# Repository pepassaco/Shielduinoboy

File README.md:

# Shielduinoboy
Just a PCB Shield for the Arduino UNO of an Arduinoboy

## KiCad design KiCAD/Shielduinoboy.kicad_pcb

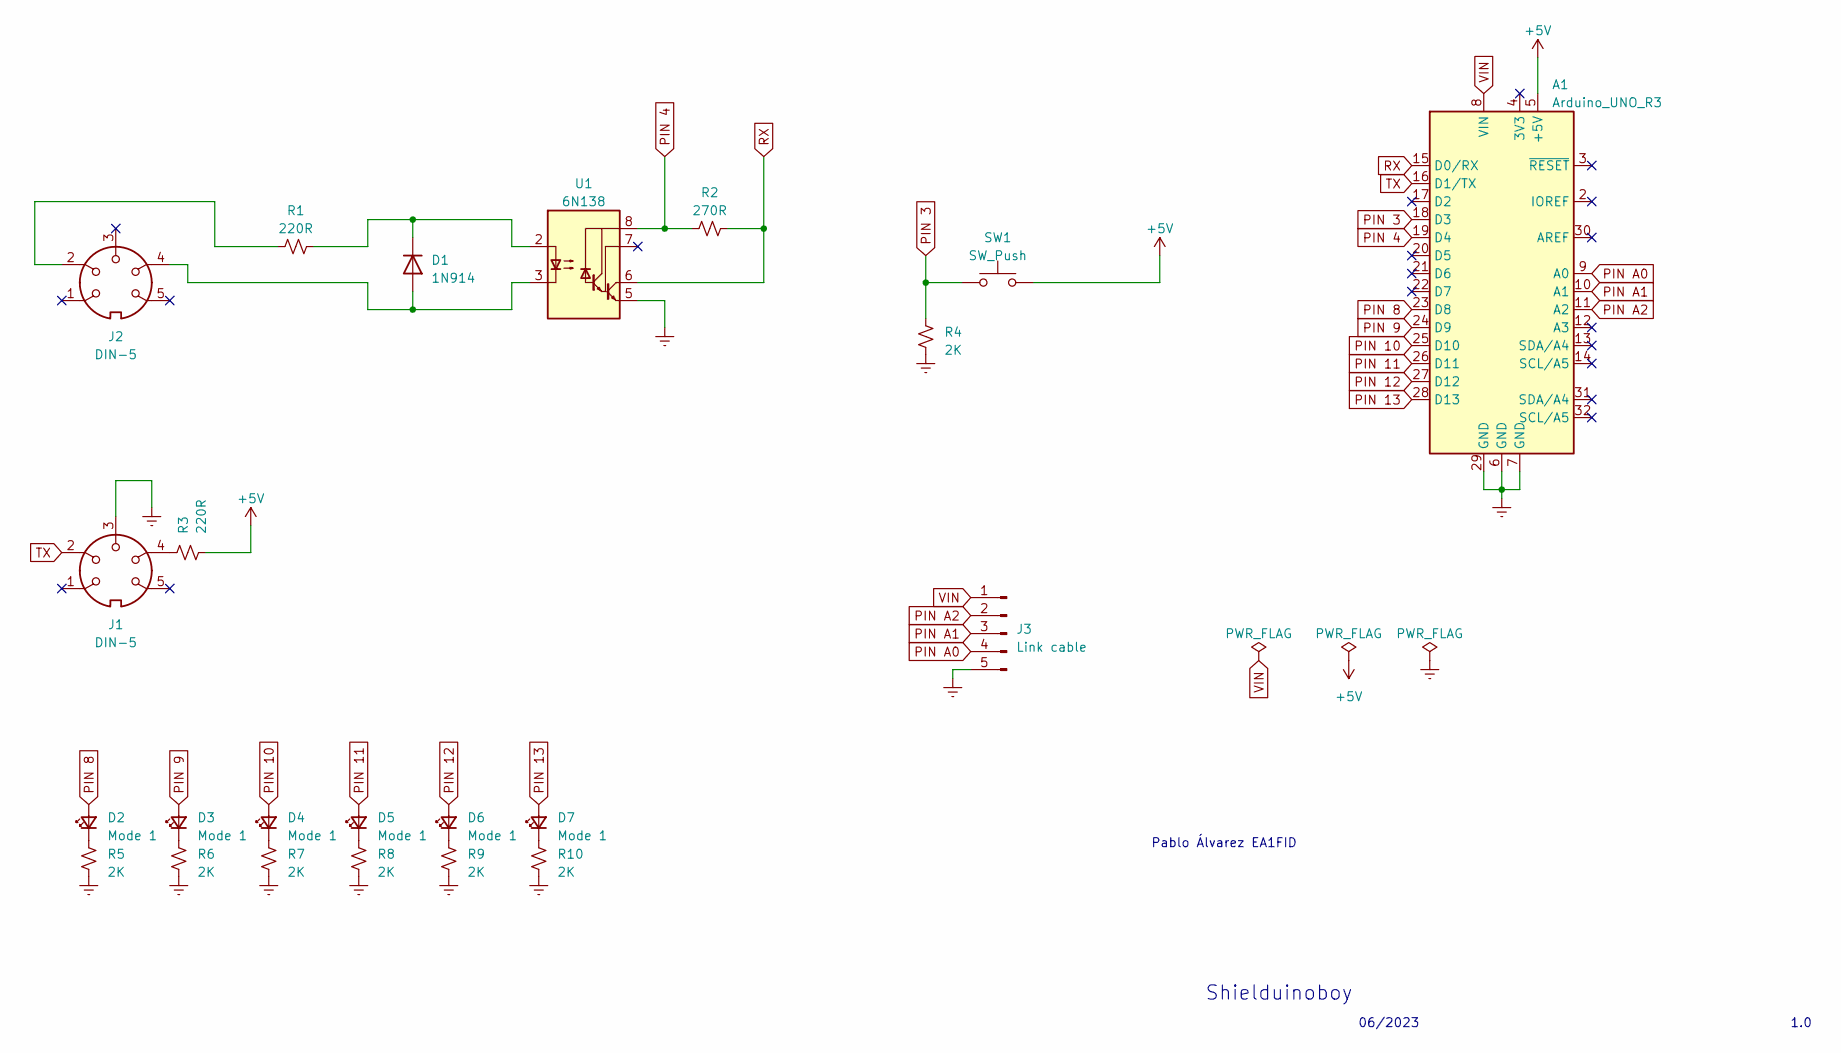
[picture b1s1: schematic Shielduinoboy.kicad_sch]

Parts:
A1: Arduino_UNO_R3; Arduino_UNO_R3_WithMountingHoles
D1: 1N914; D_DO-35_SOD27_P7.62mm_Horizontal
D2, D3, D4, D5, D6, D7: Mode 1; LED_D3.0mm
J1, J2: DIN-5; MIDI_DIN5
J3: Link cable; PinHeader_1x05_P2.54mm_Vertical
R1, R3: 220R; R_Axial_DIN0207_L6.3mm_D2.5mm_P7.62mm_Horizontal
R2: 270R; R_Axial_DIN0207_L6.3mm_D2.5mm_P7.62mm_Horizontal
R4, R5, R6, R7, R8, R9, R10: 2K; R_Axial_DIN0207_L6.3mm_D2.5mm_P7.62mm_Horizontal
SW1: SW_Push; SW_PUSH_6mm
U1: 6N138; DIP-8_W7.62mm

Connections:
+5V: A1.5 (+5V), R3.2, SW1.2
Earth: A1.6 (GND), A1.7 (GND), A1.29 (GND), J1.3, J3.5, R4.2, R5.2, R6.2, R7.2, R8.2, R9.2, R10.2, U1.5 (GND)
unnamed: D1.2 (A), J2.4, U1.3 (C2)
unnamed: D1.1 (K), R1.2, U1.2 (C1)
unnamed: D2.1 (K), R5.1
unnamed: D3.1 (K), R6.1
unnamed: D4.1 (K), R7.1
unnamed: D5.1 (K), R8.1
unnamed: D6.1 (K), R9.1
unnamed: D7.1 (K), R10.1
unnamed: J1.4, R3.1
unnamed: J2.2, R1.1
PIN 3: A1.18 (D3), R4.1, SW1.1
PIN 4: A1.19 (D4), R2.1, U1.8 (VCC)
PIN 8: A1.23 (D8), D2.2 (A)
PIN 9: A1.24 (D9), D3.2 (A)
PIN 10: A1.25 (D10), D4.2 (A)
PIN 11: A1.26 (D11), D5.2 (A)
PIN 12: A1.27 (D12), D6.2 (A)
PIN 13: A1.28 (D13), D7.2 (A)
PIN A0: A1.9 (A0), J3.4
PIN A1: A1.10 (A1), J3.3
PIN A2: A1.11 (A2), J3.2
RX: A1.15 (D0/RX), R2.2, U1.6 (VO2)
TX: A1.16 (D1/TX), J1.2
VIN: A1.8 (VIN), J3.1

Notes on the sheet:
1.0
Pablo Álvarez EA1FID
Shielduinoboy
06/2023

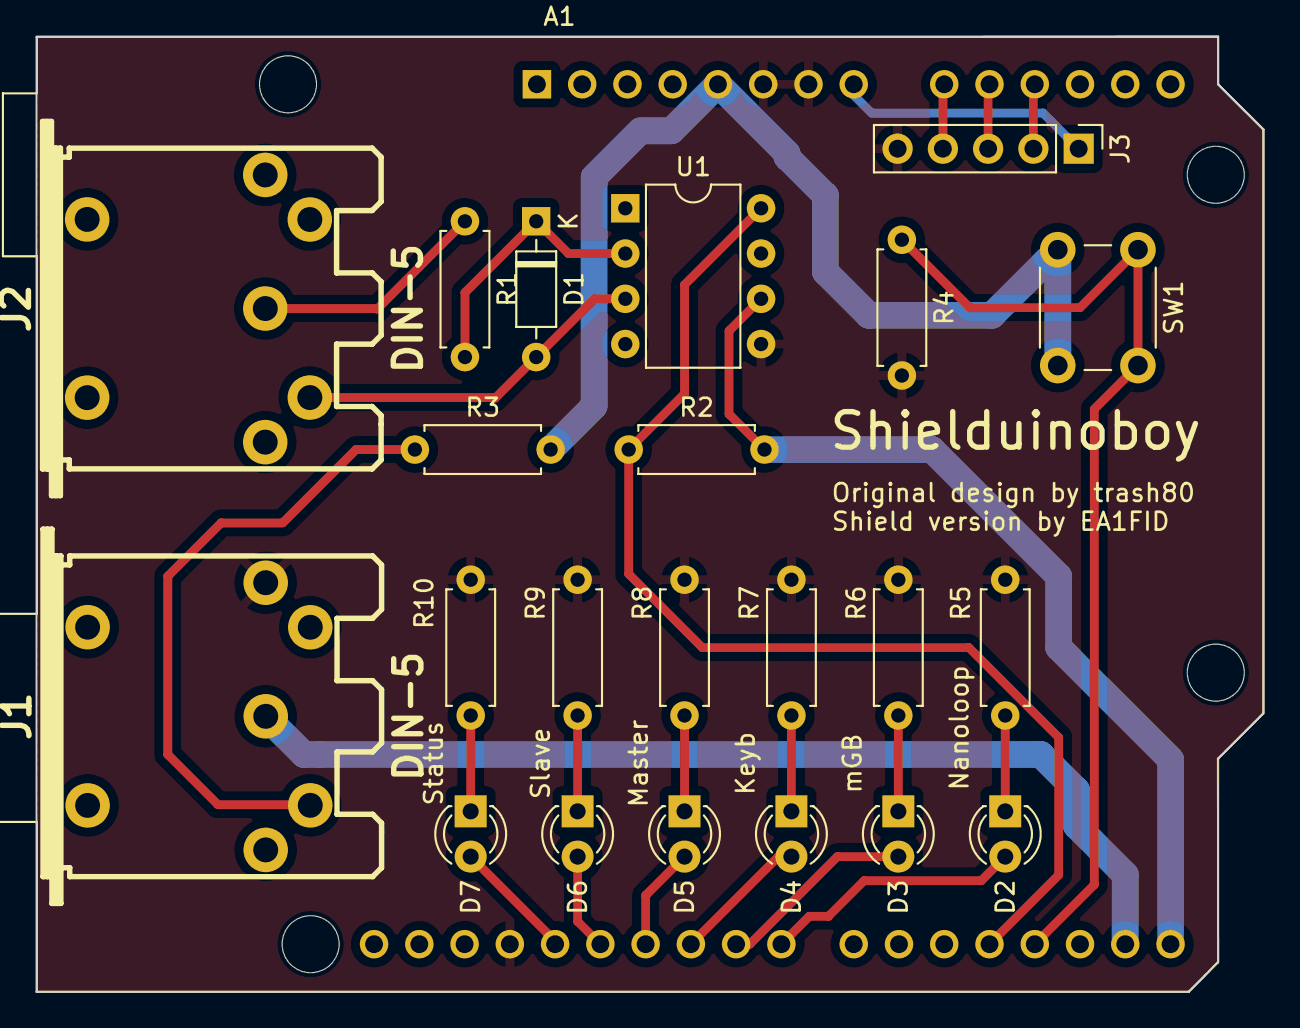
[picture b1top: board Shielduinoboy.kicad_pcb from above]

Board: 2 copper layers, 68.9 x 53.6 mm, 23 parts (0 on the bottom side), 26 nets.
